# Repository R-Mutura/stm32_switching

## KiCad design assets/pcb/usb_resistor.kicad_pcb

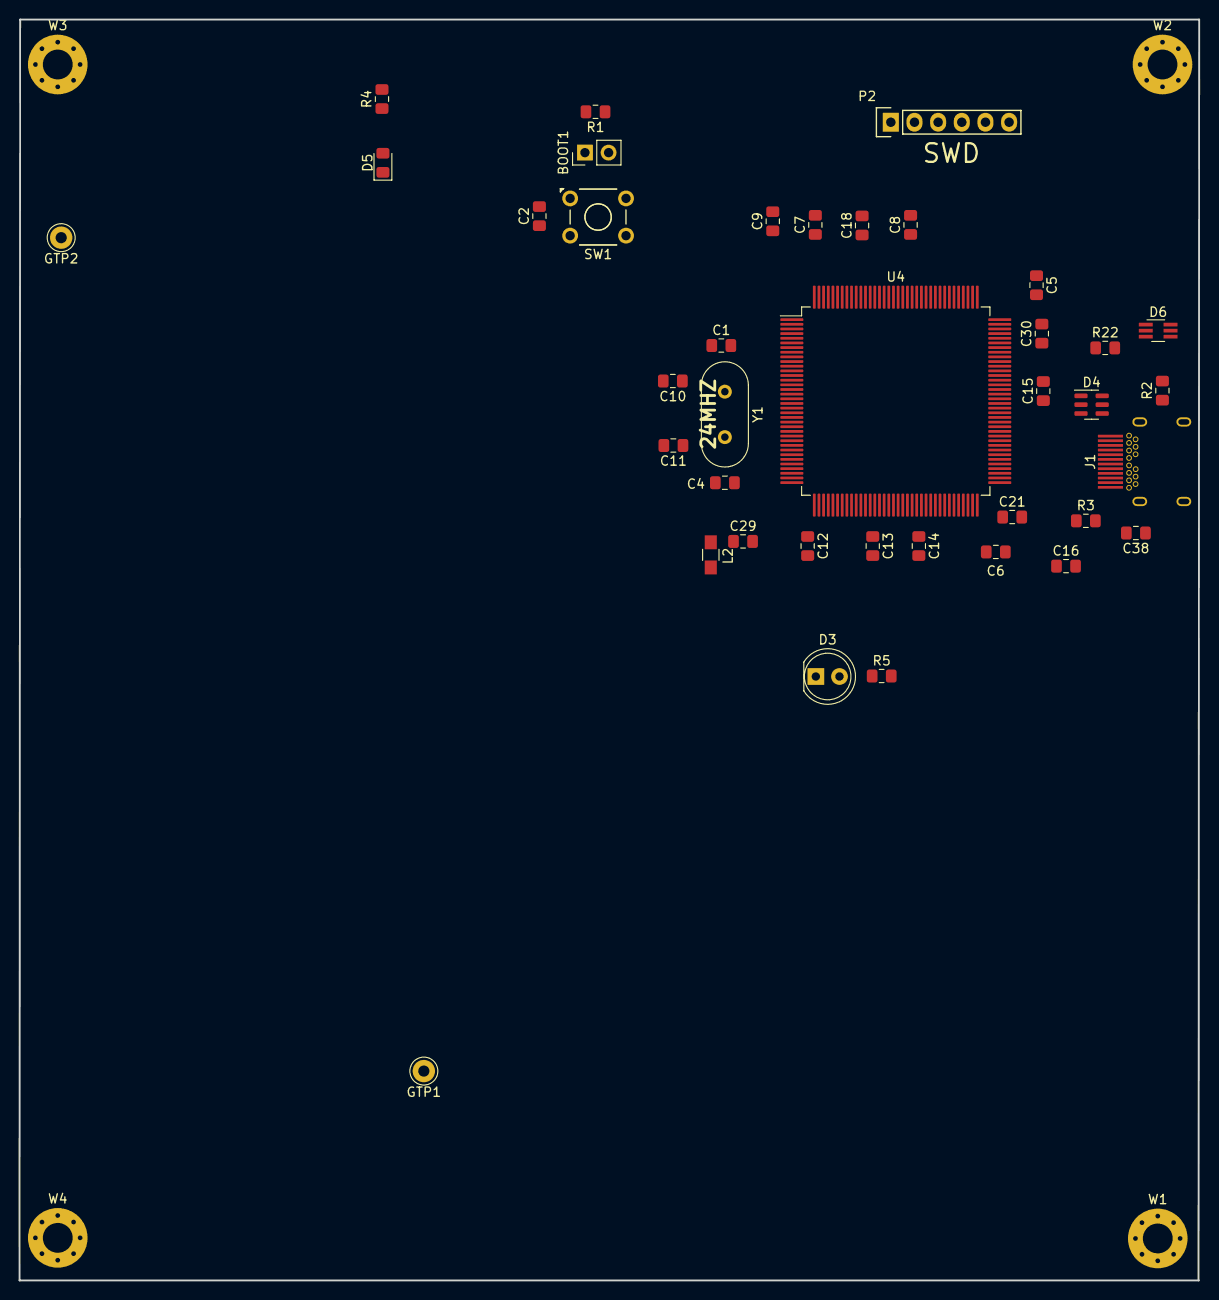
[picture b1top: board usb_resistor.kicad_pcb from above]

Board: 4 copper layers, 126.7 x 135.4 mm, 43 parts (0 on the bottom side), 22 nets, no tracks yet.

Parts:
BOOT1: Main BOOT; PinHeader_1x02_P2.54mm_Vertical
C1, C4: 22pf; C_0805_2012Metric_Pad1.15x1.40mm_HandSolder
C2, C7, C8, C9, C10, C11, C12, C13, C14, C15, C16: 0.1uf; C_0805_2012Metric_Pad1.15x1.40mm_HandSolder
C5, C6, C21: 2.2uf; C_0805_2012Metric_Pad1.15x1.40mm_HandSolder
C18: 4.7uf; C_0805_2012Metric_Pad1.15x1.40mm_HandSolder
C29, C30, C38: 1uf; C_0805_2012Metric_Pad1.15x1.40mm_HandSolder
D3: USER_LED; LED_D5.0mm
D4: IP4220CZ6_125; SC-74-6_1.5x2.9mm_P0.95mm
D5: POW_LED; LED_0805_2012Metric_Pad1.15x1.40mm_HandSolder
D6: PESD3V3L5UY; SOT-363_SC-70-6_Handsoldering
GTP1, GTP2: GND_TP; Pin_D1.0mm_L10.0mm_LooseFit
J1: USB_C_Receptacle; Wurth-632723300011-HandSoldering-Renum
L2: Main_FB; L_0805_HandSoldering
P2: SWD; Socket_Strip_Straight_1x06
R1: 10k; R_0805_2012Metric_Pad1.15x1.40mm_HandSolder
R2, R3: 5.1k; R_0805_2012Metric_Pad1.15x1.40mm_HandSolder
R4, R5: 1k; R_0805_2012Metric_Pad1.15x1.40mm_HandSolder
R22: 3k 1%; R_0805_2012Metric_Pad1.15x1.40mm_HandSolder
SW1: MAIN_RST; SW_TH_Tactile_Omron_B3F-10xx
U4: STM32F723ZETx; LQFP-144_20x20mm_P0.5mm_handsolder
W1, W2, W3, W4: Mounting Hole; MountingHole_3.2mm_M3_Pad_Via
Y1: 24mhz; Crystal_HC49-U_Vertical

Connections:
+3V3: BOOT1.1, C7.1, C8.1, C9.1, C10.1, C11.1, C12.1, C13.1, C14.1, C15.1, C16.1, C18.1, C30.1, C38.1, L2.1, P2.1, R4.1, U4.6, U4.17, U4.30, U4.39, U4.52, U4.62, U4.72, U4.86, U4.95, U4.108, U4.121, U4.131, U4.143, U4.144
/ADC1: D6.1, J1.A5, R3.1, U4.46
/ADC2: D6.3, J1.B5, R2.1, U4.47
/SWCLK: P2.2, U4.109
/SWDIO: P2.4, U4.105
/SWO: P2.6, U4.133
/VREF: C29.1, L2.2, U4.32, U4.33
D_N: D4.3, J1.A7, J1.B7, U4.77
D_P: D4.1, J1.A6, J1.B6, U4.78
GND: C1.2, C2.1, C4.2, C5.2, C6.2, C7.2, C8.2, C9.2, C10.2, C11.2, C12.2, C13.2, C14.2, C15.2, C16.2, C18.2, C21.2, C29.2, C30.2, C38.2, D3.1, D4.2, D5.1, D6.2, GTP1.1, GTP2.1, J1.A1, J1.A12, J1.B1, J1.B12, J1.S1, P2.3, R1.2, R2.2, R3.2, R22.2, SW1.3, U4.16, U4.31, U4.38, U4.51, U4.61, U4.85, U4.94, U4.107, U4.120, U4.130, W1.1, W2.1, W3.1, W4.1
unnamed: BOOT1.2, R1.1, U4.138
unnamed: C1.1, U4.23, Y1.1
unnamed: C2.2, P2.5, SW1.2, U4.25
unnamed: C4.1, U4.24, Y1.2
unnamed: C5.1, U4.106
unnamed: C6.1, U4.71
unnamed: C21.1, U4.76
unnamed: D3.2, R5.1
unnamed: D5.2, R4.2
unnamed: R5.2, U4.54
unnamed: R22.1, U4.75
VB_5V_PRI: D4.5, J1.A4, J1.A9, J1.B4, J1.B9

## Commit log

2022-01-25 initial commit: schematic complete
2022-01-26 updated footprint assignment
